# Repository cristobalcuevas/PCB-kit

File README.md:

# PCB-kit
PCb with elemental components for arduino

## PCB

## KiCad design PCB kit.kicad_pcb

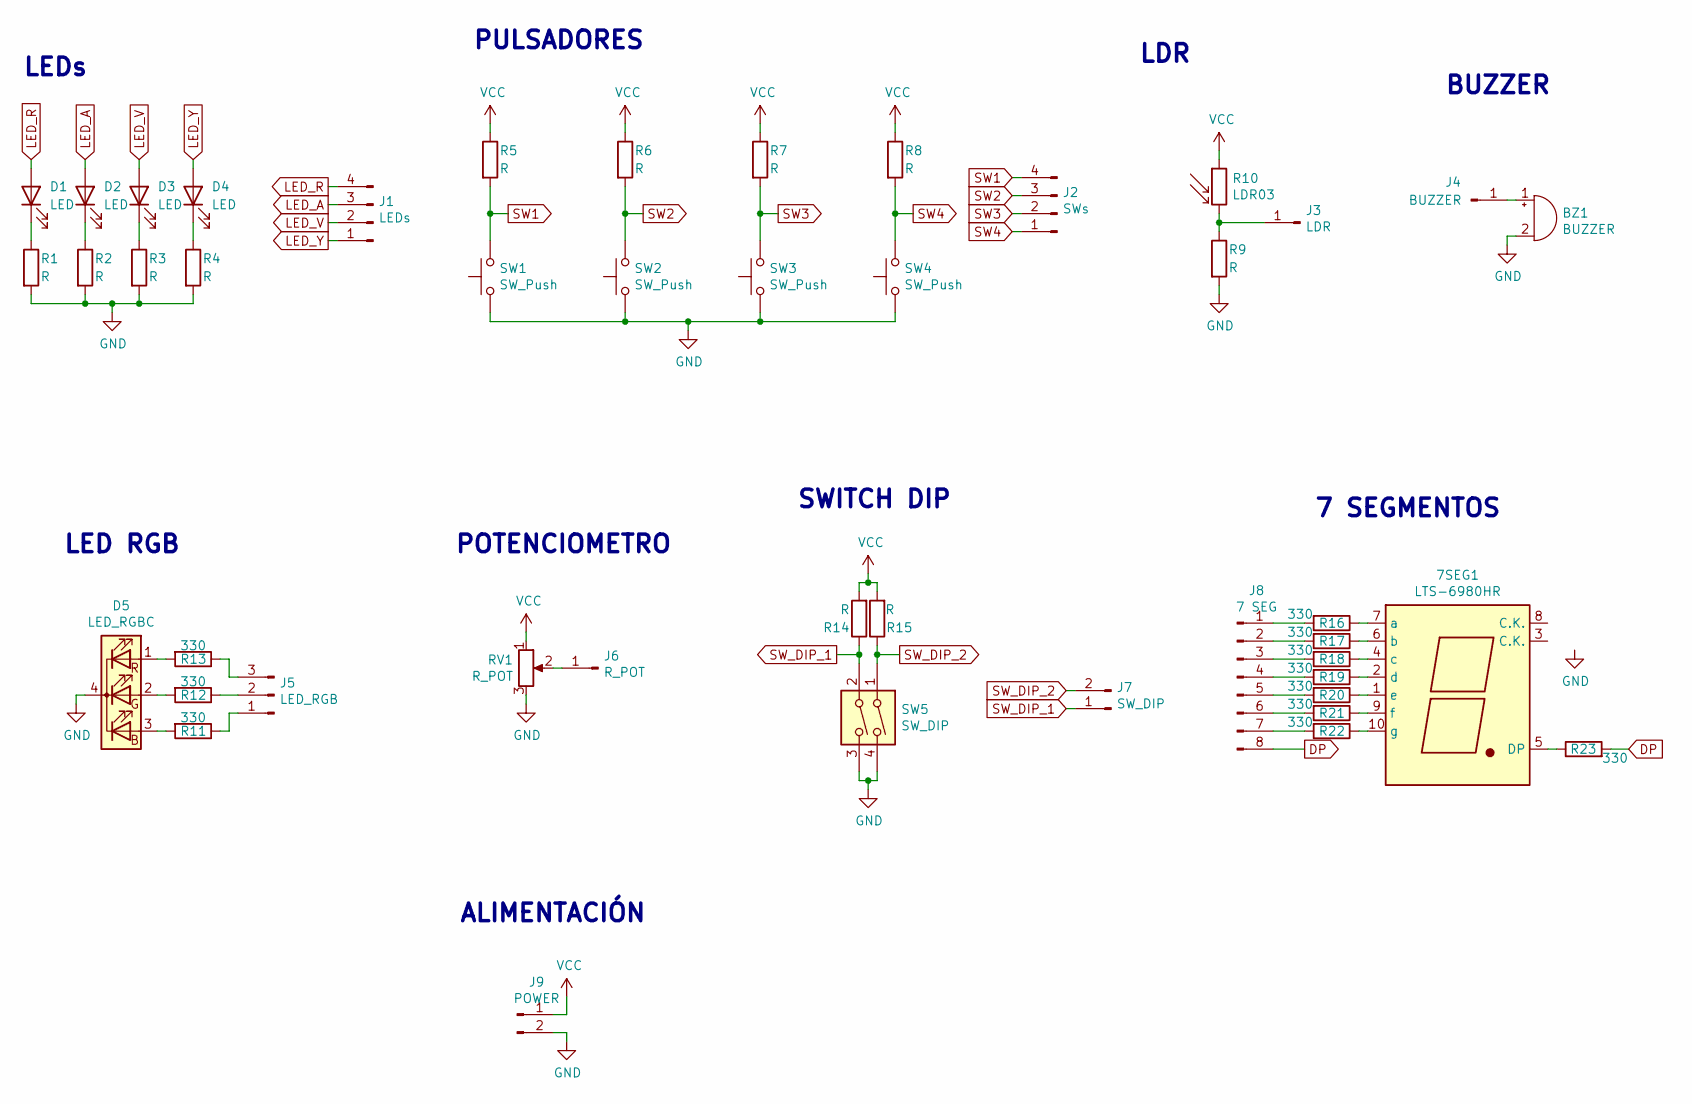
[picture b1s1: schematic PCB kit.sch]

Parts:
7SEG1: LTS-6980HR; 7SegmentLED_LTS6760_LTS6780
BZ1: BUZZER; Buzzer_TDK_PS1240P02BT_D12.2mm_H6.5mm
D1, D2, D3, D4: LED; LED_D5.0mm
D5: LED_RGBC; LED_D5.0mm-4_RGB_Staggered_Pins
J1: LEDs; PinHeader_1x04_P2.54mm_Vertical
J2: SWs; PinHeader_1x04_P2.54mm_Vertical
J3: LDR; PinHeader_1x01_P2.54mm_Vertical
J4: BUZZER; PinHeader_1x01_P2.54mm_Vertical
J5: LED_RGB; PinHeader_1x03_P2.54mm_Vertical
J6: R_POT; PinHeader_1x01_P2.54mm_Vertical
J7: SW_DIP; PinHeader_1x02_P2.54mm_Vertical
J8: 7 SEG; PinHeader_1x08_P2.54mm_Vertical
J9: POWER; PinHeader_1x02_P2.54mm_Vertical
R1, R2, R3, R4, R5, R6, R7, R8, R9, R14, R15: R; R_Axial_DIN0207_L6.3mm_D2.5mm_P7.62mm_Horizontal
R10: LDR03; R_LDR_5.1x4.3mm_P3.4mm_Vertical
R11, R12, R13, R16, R17, R18, R19, R20, R21, R22, R23: 330; R_Axial_DIN0207_L6.3mm_D2.5mm_P7.62mm_Horizontal
RV1: R_POT; PinHeader_1x03_P2.54mm_Vertical
SW1, SW2, SW3, SW4: SW_Push; SW_PUSH_6mm
SW5: SW_DIP; SW_DIP_SPSTx02_Slide_9.78x7.26mm_W7.62mm_P2.54mm

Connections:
DP: J8.8, R23.2
GND: BZ1.2 (+), D5.4 (K), J9.2, R1.2, R2.2, R3.2, R4.2, R9.2, RV1.3, SW1.1, SW2.1, SW3.1, SW4.1, SW5.3, SW5.4
LED_A: D2.2 (A), J1.3
LED_R: D1.2 (A), J1.4
LED_V: D3.2 (A), J1.2
LED_Y: D4.2 (A), J1.1
unnamed: 7SEG1.1 (e), R20.1
unnamed: 7SEG1.2 (d), R19.1
unnamed: 7SEG1.4 (c), R18.1
unnamed: 7SEG1.5 (DP), R23.1
unnamed: 7SEG1.6 (b), R17.1
unnamed: 7SEG1.7 (a), R16.1
unnamed: 7SEG1.9 (f), R21.1
unnamed: 7SEG1.10 (g), R22.1
unnamed: BZ1.1 (-), J4.1
unnamed: D1.1 (K), R1.1
unnamed: D2.1 (K), R2.1
unnamed: D3.1 (K), R3.1
unnamed: D4.1 (K), R4.1
unnamed: D5.1 (RA), R13.2
unnamed: D5.2 (GA), R12.2
unnamed: D5.3 (BA), R11.2
unnamed: J3.1, R9.1, R10.2
unnamed: J5.1, R11.1
unnamed: J5.2, R12.1
unnamed: J5.3, R13.1
unnamed: J6.1, RV1.2
unnamed: J8.1, R16.2
unnamed: J8.2, R17.2
unnamed: J8.3, R18.2
unnamed: J8.4, R19.2
unnamed: J8.5, R20.2
unnamed: J8.6, R21.2
unnamed: J8.7, R22.2
SW1: J2.4, R5.2, SW1.2
SW2: J2.3, R6.2, SW2.2
SW3: J2.2, R7.2, SW3.2
SW4: J2.1, R8.2, SW4.2
SW_DIP_1: J7.1, R14.1, SW5.2
SW_DIP_2: J7.2, R15.1, SW5.1
VCC: J9.1, R5.1, R6.1, R7.1, R8.1, R10.1, R14.2, R15.2, RV1.1

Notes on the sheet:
LEDs
PULSADORES
LDR
BUZZER
LED RGB
POTENCIOMETRO
SWITCH DIP
7 SEGMENTOS
ALIMENTACIÓN

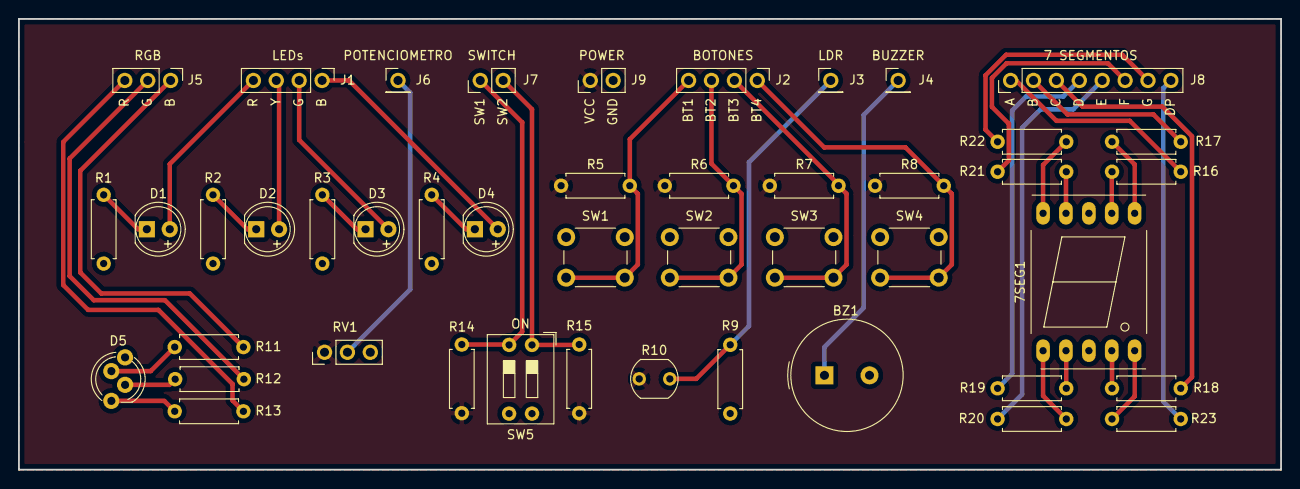
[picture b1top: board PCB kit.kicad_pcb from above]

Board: 2 copper layers, 140.0 x 50.0 mm, 45 parts (0 on the bottom side), 41 nets.

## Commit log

2021-04-22 version 1
2021-04-23 version 2
